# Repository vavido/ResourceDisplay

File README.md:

# Resource Display (working name)
Just a stupid idea i had to use some 7-Segment displays i had to make a live display for the resource use on my PC.

This repo includes the board layout (in `EAGLE Files`) files, CAD drawings of the case (in `case`), the arduino sketch in `ResourceDisplay` and the Desktop application to go with it in `ArudinoSerial`.

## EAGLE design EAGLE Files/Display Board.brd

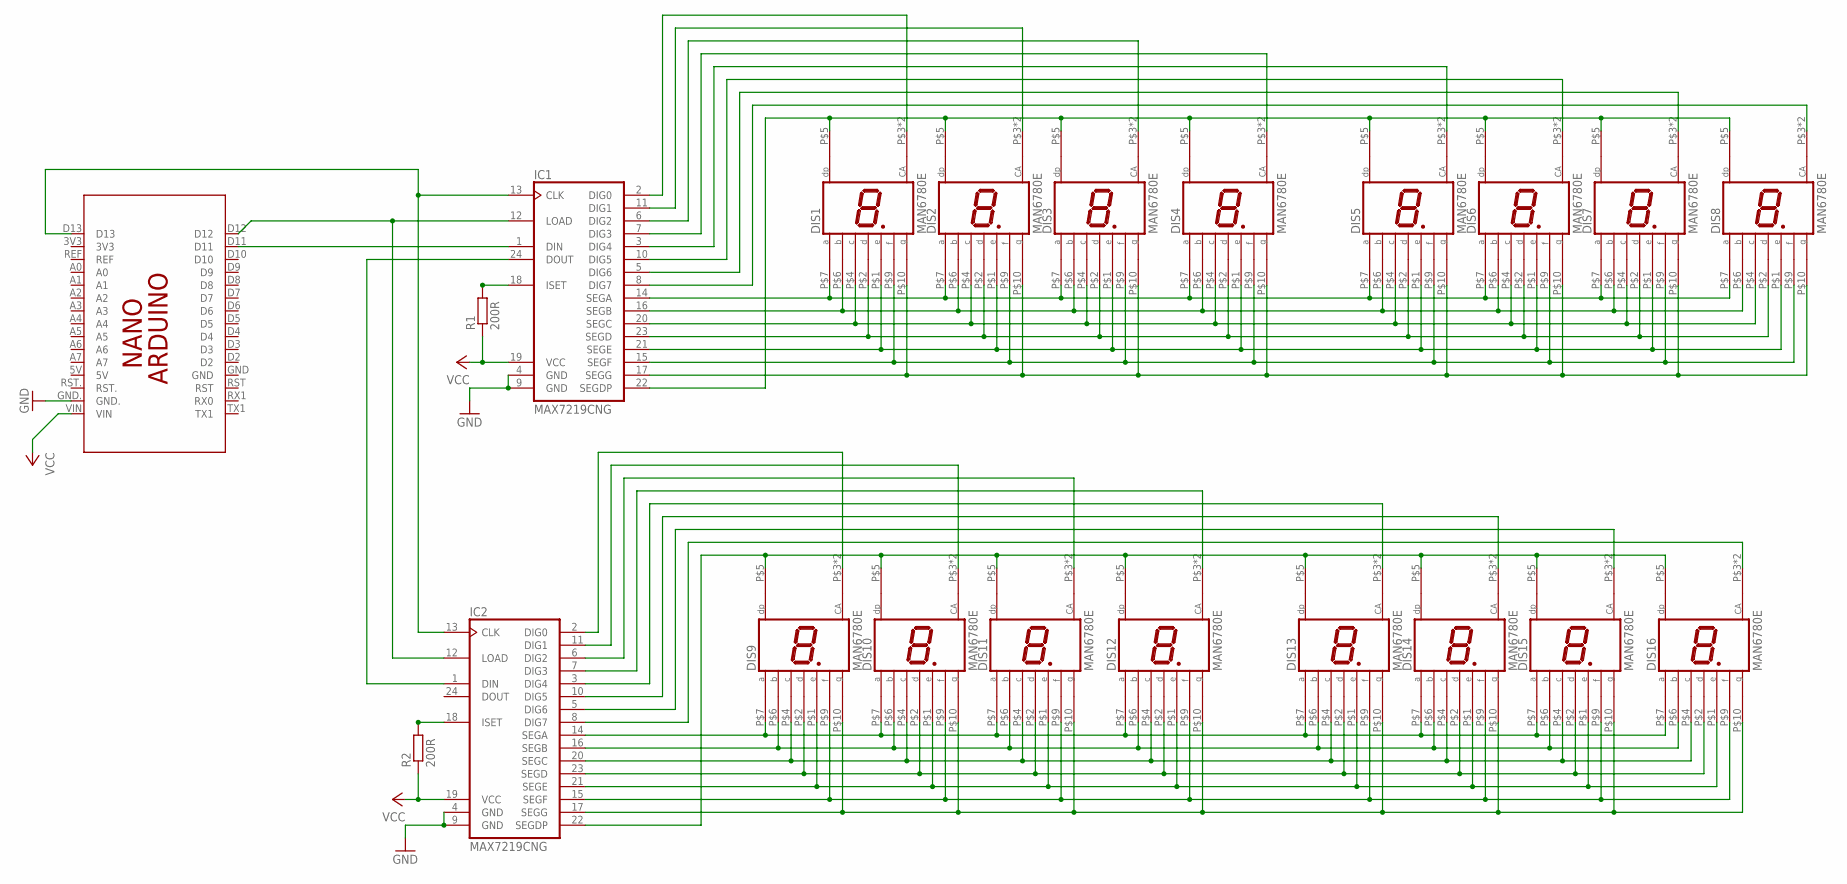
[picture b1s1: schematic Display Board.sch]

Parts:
DIS1, DIS2, DIS3, DIS4, DIS5, DIS6, DIS7, DIS8, DIS9, DIS10, DIS11, DIS12, DIS13, DIS14, DIS15, DIS16: MAN6780E; MAN6780
IC1, IC2: MAX7219CNG; DIL24-3
PCB1: ARDUINO_NANO
R1, R2: 200R; M1206

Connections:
GND: IC1.4 (GND), IC1.9 (GND), IC2.4 (GND), IC2.9 (GND), PCB1.GND.
unnamed: DIS1.P$7 (A), DIS2.P$7 (A), DIS3.P$7 (A), DIS4.P$7 (A), DIS5.P$7 (A), DIS6.P$7 (A), DIS7.P$7 (A), DIS8.P$7 (A), IC1.14 (SEGA)
unnamed: DIS1.P$6 (B), DIS2.P$6 (B), DIS3.P$6 (B), DIS4.P$6 (B), DIS5.P$6 (B), DIS6.P$6 (B), DIS7.P$6 (B), DIS8.P$6 (B), IC1.16 (SEGB)
unnamed: DIS1.P$4 (C), DIS2.P$4 (C), DIS3.P$4 (C), DIS4.P$4 (C), DIS5.P$4 (C), DIS6.P$4 (C), DIS7.P$4 (C), DIS8.P$4 (C), IC1.20 (SEGC)
unnamed: DIS1.P$2 (D), DIS2.P$2 (D), DIS3.P$2 (D), DIS4.P$2 (D), DIS5.P$2 (D), DIS6.P$2 (D), DIS7.P$2 (D), DIS8.P$2 (D), IC1.23 (SEGD)
unnamed: DIS1.P$1 (E), DIS2.P$1 (E), DIS3.P$1 (E), DIS4.P$1 (E), DIS5.P$1 (E), DIS6.P$1 (E), DIS7.P$1 (E), DIS8.P$1 (E), IC1.21 (SEGE)
unnamed: DIS1.P$9 (F), DIS2.P$9 (F), DIS3.P$9 (F), DIS4.P$9 (F), DIS5.P$9 (F), DIS6.P$9 (F), DIS7.P$9 (F), DIS8.P$9 (F), IC1.15 (SEGF)
unnamed: DIS1.P$10 (G), DIS2.P$10 (G), DIS3.P$10 (G), DIS4.P$10 (G), DIS5.P$10 (G), DIS6.P$10 (G), DIS7.P$10 (G), DIS8.P$10 (G), IC1.17 (SEGG)
unnamed: DIS1.P$5 (DP), DIS2.P$5 (DP), DIS3.P$5 (DP), DIS4.P$5 (DP), DIS5.P$5 (DP), DIS6.P$5 (DP), DIS7.P$5 (DP), DIS8.P$5 (DP), IC1.22 (SEGDP)
unnamed: DIS1.P$3 (CA), DIS1.P$8 (CA), IC1.2 (DIG0)
unnamed: DIS2.P$3 (CA), DIS2.P$8 (CA), IC1.11 (DIG1)
unnamed: DIS3.P$3 (CA), DIS3.P$8 (CA), IC1.6 (DIG2)
unnamed: DIS4.P$3 (CA), DIS4.P$8 (CA), IC1.7 (DIG3)
unnamed: DIS5.P$3 (CA), DIS5.P$8 (CA), IC1.3 (DIG4)
unnamed: DIS6.P$3 (CA), DIS6.P$8 (CA), IC1.10 (DIG5)
unnamed: DIS9.P$7 (A), DIS10.P$7 (A), DIS11.P$7 (A), DIS12.P$7 (A), DIS13.P$7 (A), DIS14.P$7 (A), DIS15.P$7 (A), DIS16.P$7 (A), IC2.14 (SEGA)
unnamed: DIS8.P$3 (CA), DIS8.P$8 (CA), IC1.8 (DIG7)
unnamed: DIS9.P$6 (B), DIS10.P$6 (B), DIS11.P$6 (B), DIS12.P$6 (B), DIS13.P$6 (B), DIS14.P$6 (B), DIS15.P$6 (B), DIS16.P$6 (B), IC2.16 (SEGB)
unnamed: DIS7.P$3 (CA), DIS7.P$8 (CA), IC1.5 (DIG6)
unnamed: DIS9.P$4 (C), DIS10.P$4 (C), DIS11.P$4 (C), DIS12.P$4 (C), DIS13.P$4 (C), DIS14.P$4 (C), DIS15.P$4 (C), DIS16.P$4 (C), IC2.20 (SEGC)
unnamed: DIS9.P$2 (D), DIS10.P$2 (D), DIS11.P$2 (D), DIS12.P$2 (D), DIS13.P$2 (D), DIS14.P$2 (D), DIS15.P$2 (D), DIS16.P$2 (D), IC2.23 (SEGD)
unnamed: DIS9.P$1 (E), DIS10.P$1 (E), DIS11.P$1 (E), DIS12.P$1 (E), DIS13.P$1 (E), DIS14.P$1 (E), DIS15.P$1 (E), DIS16.P$1 (E), IC2.21 (SEGE)
unnamed: DIS9.P$9 (F), DIS10.P$9 (F), DIS11.P$9 (F), DIS12.P$9 (F), DIS13.P$9 (F), DIS14.P$9 (F), DIS15.P$9 (F), DIS16.P$9 (F), IC2.15 (SEGF)
unnamed: IC1.18 (ISET), R1.2
unnamed: DIS9.P$10 (G), DIS10.P$10 (G), DIS11.P$10 (G), DIS12.P$10 (G), DIS13.P$10 (G), DIS14.P$10 (G), DIS15.P$10 (G), DIS16.P$10 (G), IC2.17 (SEGG)
unnamed: DIS9.P$5 (DP), DIS10.P$5 (DP), DIS11.P$5 (DP), DIS12.P$5 (DP), DIS13.P$5 (DP), DIS14.P$5 (DP), DIS15.P$5 (DP), DIS16.P$5 (DP), IC2.22 (SEGDP)
unnamed: DIS9.P$3 (CA), DIS9.P$8 (CA), IC2.2 (DIG0)
unnamed: DIS10.P$3 (CA), DIS10.P$8 (CA), IC2.11 (DIG1)
unnamed: DIS11.P$3 (CA), DIS11.P$8 (CA), IC2.6 (DIG2)
unnamed: DIS12.P$3 (CA), DIS12.P$8 (CA), IC2.7 (DIG3)
unnamed: DIS13.P$3 (CA), DIS13.P$8 (CA), IC2.3 (DIG4)
unnamed: DIS14.P$3 (CA), DIS14.P$8 (CA), IC2.10 (DIG5)
unnamed: DIS16.P$3 (CA), DIS16.P$8 (CA), IC2.8 (DIG7)
unnamed: DIS15.P$3 (CA), DIS15.P$8 (CA), IC2.5 (DIG6)
unnamed: IC2.18 (ISET), R2.2
unnamed: IC1.24 (DOUT), IC2.1 (DIN)
unnamed: IC1.13 (CLK), IC2.13 (CLK), PCB1.D13
unnamed: IC1.12 (LOAD), IC2.12 (LOAD), PCB1.D12
unnamed: IC1.1 (DIN), PCB1.D11
VCC: IC1.19 (VCC), IC2.19 (VCC), PCB1.VIN, R1.1, R2.1

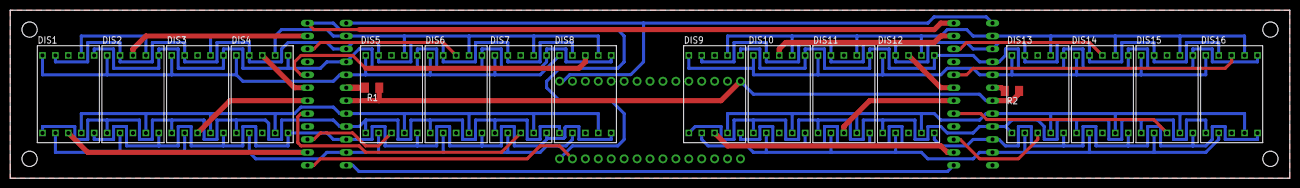
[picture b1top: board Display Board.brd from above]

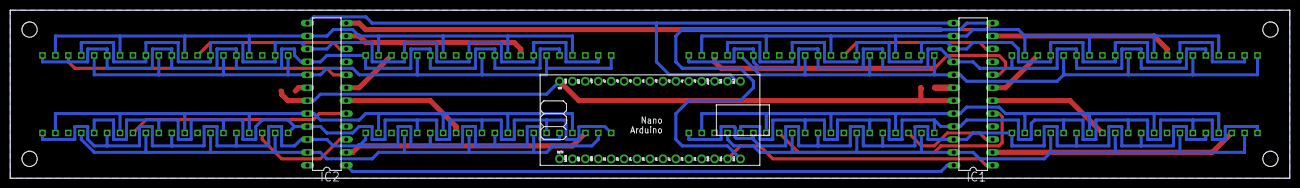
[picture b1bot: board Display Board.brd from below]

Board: 2 copper layers, 251.5 x 33.0 mm, 21 parts (3 on the bottom side), 40 nets.

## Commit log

2017-05-26 add gitignore
2017-05-26 renamed folder
2017-05-27 fixed typos in arduino project
2017-05-27 ignore cache files
2017-05-27 Completed parsing locig on arduino side
2017-05-30 Ignore build files, fix arduino compiler errors
2017-05-30 added SerialConnection class
2017-05-30 added test interface
2017-05-30 chanded baudrate
2017-05-30 changed display brightness
2017-06-15 started designing case
2017-06-17 added system monitor, some refactoring
2017-06-17 chanded logic for displaying float values
2017-06-17 update documentation
2017-07-19 add test sketch
2017-07-26 case design and code tests
2017-07-27 Auto stash before merge of "master" and "origin/master"
2017-08-23 finish case design
2017-08-28 first test with real performance counter
2017-09-20 change case for easier printing
2017-10-12 chamfer edges
2018-10-23 add ring buffer class
2018-10-23 restructure repo
2018-10-23 add documentation
2018-10-23 code cleanup
